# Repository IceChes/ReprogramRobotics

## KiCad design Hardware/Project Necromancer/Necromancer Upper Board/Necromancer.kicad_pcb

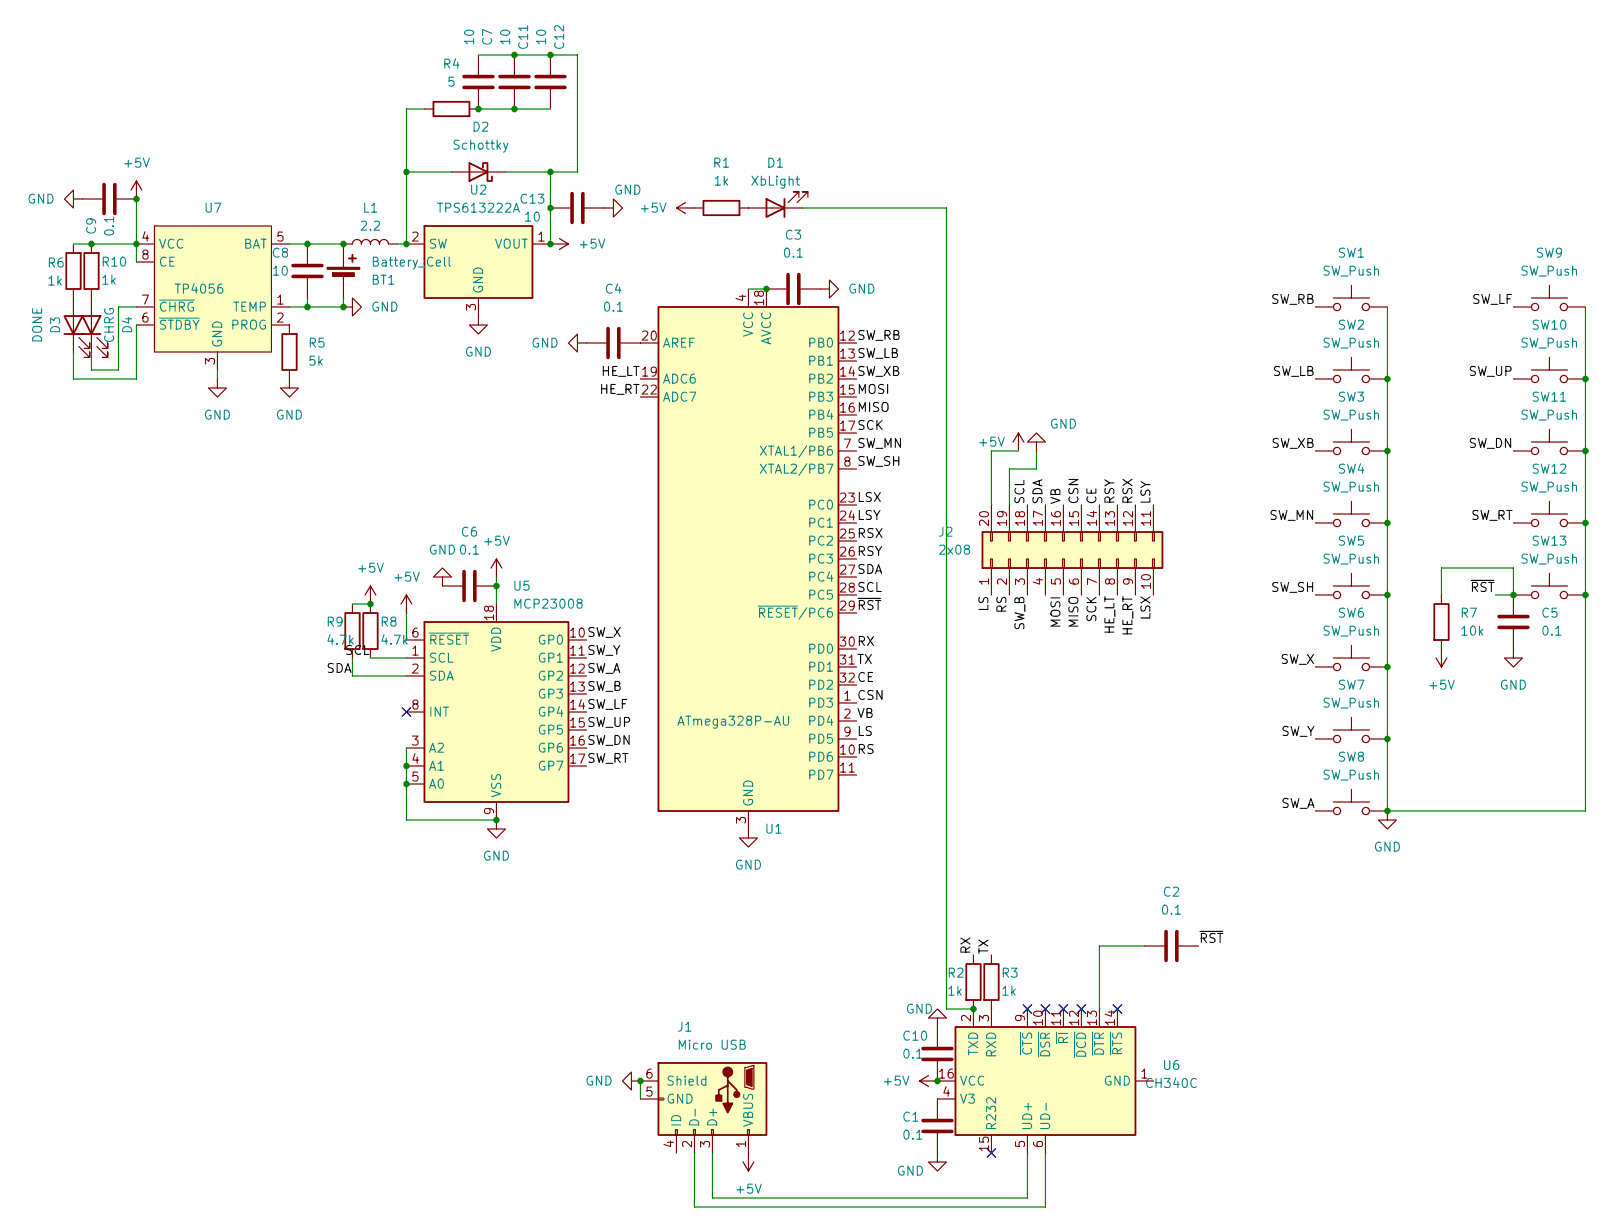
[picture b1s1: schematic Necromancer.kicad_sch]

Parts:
BT1: Battery_Cell; PinHeader_1x02_P2.54mm_Vertical
C1, C2, C3, C4, C5, C6, C9, C10: 0.1; C_0805_2012Metric
C7, C8, C11, C12, C13: 10; C_0805_2012Metric
D1: XbLight; LED_0805_2012Metric
D2: Schottky; D_SOD-323
D3: DONE; LED_0805_2012Metric
D4: CHRG; LED_0805_2012Metric
J1: Micro USB; USB_Micro-B_Amphenol_10118193-0001LF_Horizontal
J2: 2x08; PinHeader_2x10_P2.54mm_Vertical
L1: 2.2; L_2010_5025Metric
R1, R2, R3, R6, R10: 1k; R_0805_2012Metric
R4: 5; R_0805_2012Metric
R5: 5k; R_0805_2012Metric
R7: 10k; R_0805_2012Metric
R8, R9: 4.7k; R_0805_2012Metric
SW1, SW2: SW_Push; SW_Tactile_SPST_Angled_PTS645Vx31-2LFS
SW3: SW_Push; membraneSwitch_Large
SW4, SW5, SW6, SW7, SW8: SW_Push; membraneSwitch_Small
SW9, SW10, SW11, SW12: SW_Push; metaldome_7mm
SW13: SW_Push; SW_Push_1P1T_NO_Vertical_Wuerth_434133025816
U1: ATmega328P-AU; TQFP-32_7x7mm_P0.8mm
U2: TPS613222A; SOT-23
U5: MCP23008; SOIC-18W_7.5x11.6mm_P1.27mm
U6: CH340C; SOIC-16_3.9x9.9mm_P1.27mm
U7: TP4056; SOP-8_5.28x5.23mm_P1.27mm

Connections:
+5V: C6.2, C7.1, C9.1, C10.1, C11.1, C12.1, C13.1, D2.1 (K), J1.1 (VBUS), J2.20, R1.1, R6.2, R7.2, R8.1, R9.1, R10.2, U2.1 (VOUT), U5.6 (~RESET), U5.18 (VDD), U6.16 (VCC), U7.4 (VCC), U7.8 (CE)
/CE: J2.14, U1.32 (PD2)
/CSN: J2.15, U1.1 (PD3)
/HE_LT: J2.8, U1.19 (ADC6)
/HE_RT: J2.9, U1.22 (ADC7)
/LS: J2.1, U1.9 (PD5)
/LSX: J2.10, U1.23 (PC0)
/LSY: J2.11, U1.24 (PC1)
/MISO: J2.6, U1.16 (PB4)
/MOSI: J2.5, U1.15 (PB3)
/RS: J2.2, U1.10 (PD6)
/RSX: J2.12, U1.25 (PC2)
/RSY: J2.13, U1.26 (PC3)
/RX: R2.1, U1.30 (PD0)
/SCK: J2.7, U1.17 (PB5)
/SCL: J2.18, R8.2, U1.28 (PC5), U5.1 (SCL)
/SDA: J2.17, R9.2, U1.27 (PC4), U5.2 (SDA)
/SW_A: SW8.1, U5.12 (GP2)
/SW_B: J2.3, U5.13 (GP3)
/SW_DN: SW11.1, U5.16 (GP6)
/SW_LB: SW2.1, U1.13 (PB1)
/SW_LF: SW9.1, U5.14 (GP4)
/SW_MN: SW4.1, U1.7 (XTAL1/PB6)
/SW_RB: SW1.1, U1.12 (PB0)
/SW_RT: SW12.1, U5.17 (GP7)
/SW_SH: SW5.1, U1.8 (XTAL2/PB7)
/SW_UP: SW10.1, U5.15 (GP5)
/SW_X: SW6.1, U5.10 (GP0)
/SW_XB: SW3.1, U1.14 (PB2)
/SW_Y: SW7.1, U5.11 (GP1)
/TX: R3.1, U1.31 (PD1)
/VB: J2.16, U1.2 (PD4)
/~RST: C2.2, C5.1, R7.1, SW13.1, U1.29 (~RESET/PC6)
GND: BT1.2 (-), C1.1, C3.2, C4.1, C5.2, C6.1, C8.1, C9.2, C10.2, C13.2, J1.5 (GND), J1.6 (Shield), J2.19, R5.1, SW1.2, SW2.2, SW3.2, SW4.2, SW5.2, SW6.2, SW7.2, SW8.2, SW9.2, SW10.2, SW11.2, SW12.2, SW13.2, U1.3 (GND), U1.5 (GND), U1.21 (GND), U2.3 (GND), U5.3 (A2), U5.4 (A1), U5.5 (A0), U5.9 (VSS), U7.1 (TEMP), U7.3 (GND)
unnamed: BT1.1 (+), C8.2, L1.1, U7.5 (BAT)
unnamed: C7.2, C11.2, C12.2, R4.2
unnamed: D1.2 (A), R1.2
unnamed: D1.1 (K), R2.2, U6.2 (TXD)
unnamed: D2.2 (A), L1.2, R4.1, U2.2 (SW)
unnamed: D3.2 (A), R6.1
unnamed: D3.1 (K), U7.6 (~STDBY)
unnamed: D4.2 (A), R10.1
unnamed: D4.1 (K), U7.7 (~CHRG)
unnamed: J1.3 (D+), U6.5 (UD+)
unnamed: J1.2 (D-), U6.6 (UD-)
unnamed: C4.2, U1.20 (AREF)
unnamed: C3.1, U1.4 (VCC), U1.6 (VCC), U1.18 (AVCC)
unnamed: R3.2, U6.3 (RXD)
unnamed: C1.2, U6.4 (V3)
unnamed: C2.1, U6.13 (~DTR)
unnamed: R5.2, U7.2 (PROG)

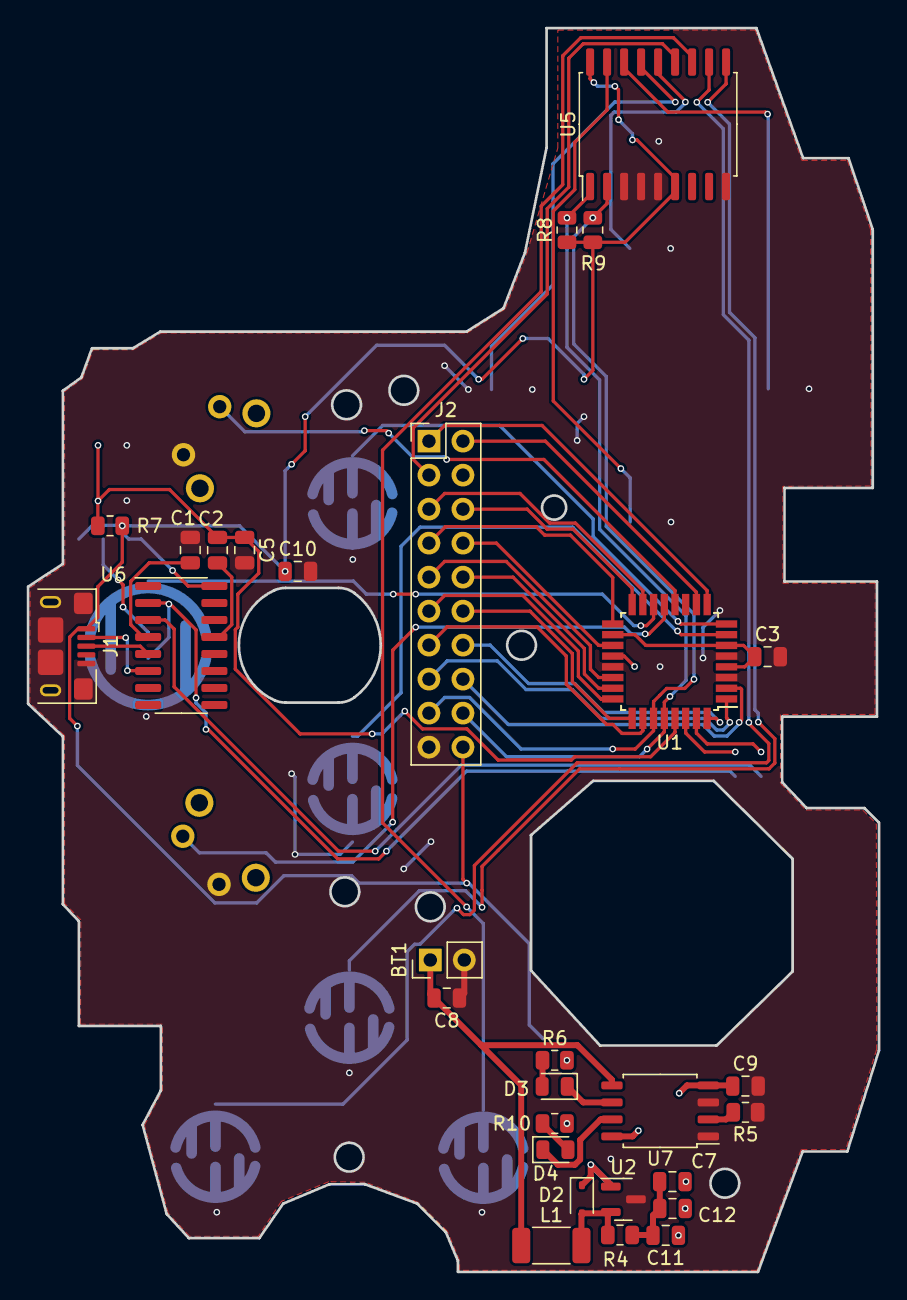
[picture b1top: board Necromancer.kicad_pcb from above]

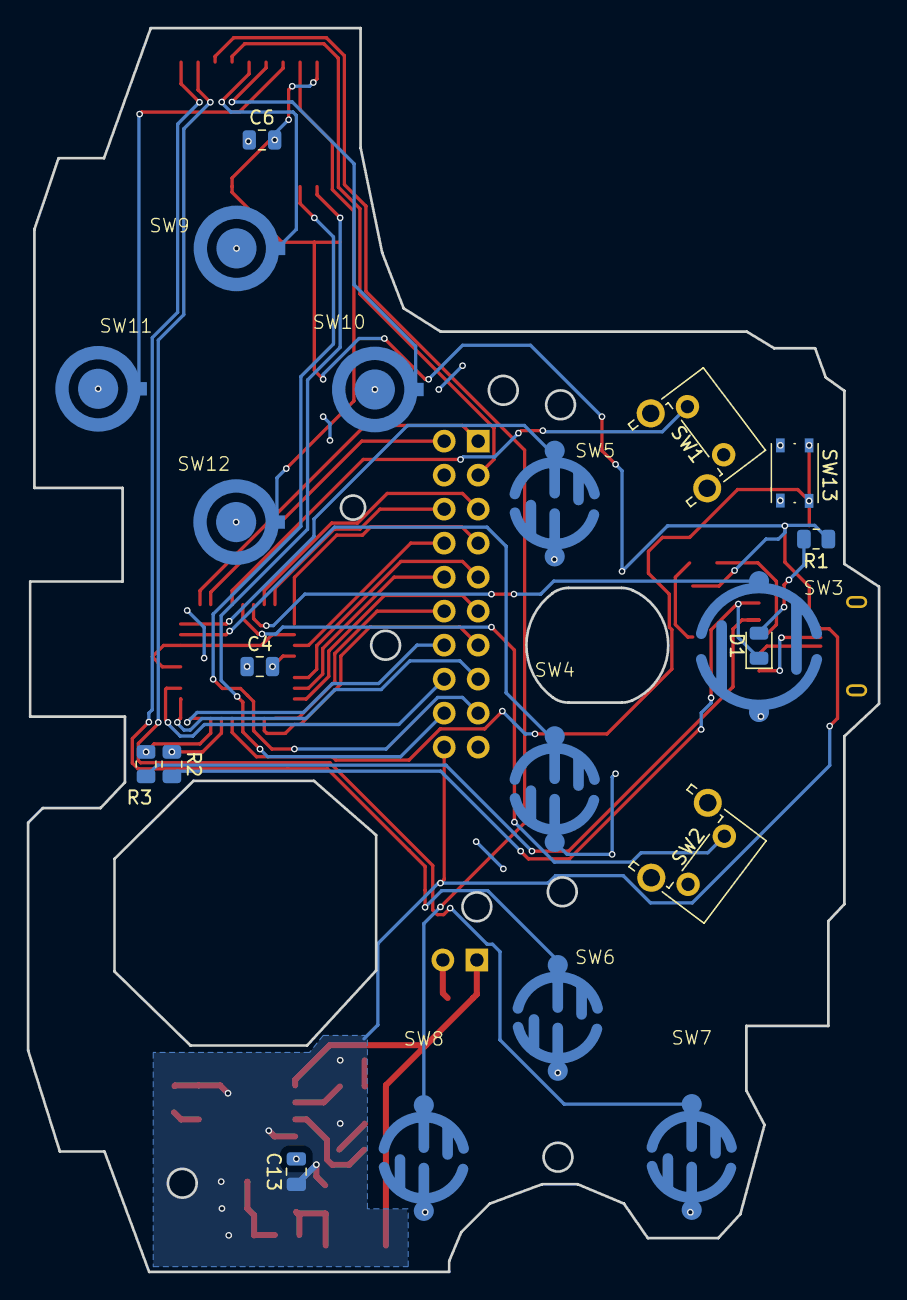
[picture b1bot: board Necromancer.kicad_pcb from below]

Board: 2 copper layers, 63.6 x 92.9 mm, 49 parts (20 on the bottom side), 51 nets.

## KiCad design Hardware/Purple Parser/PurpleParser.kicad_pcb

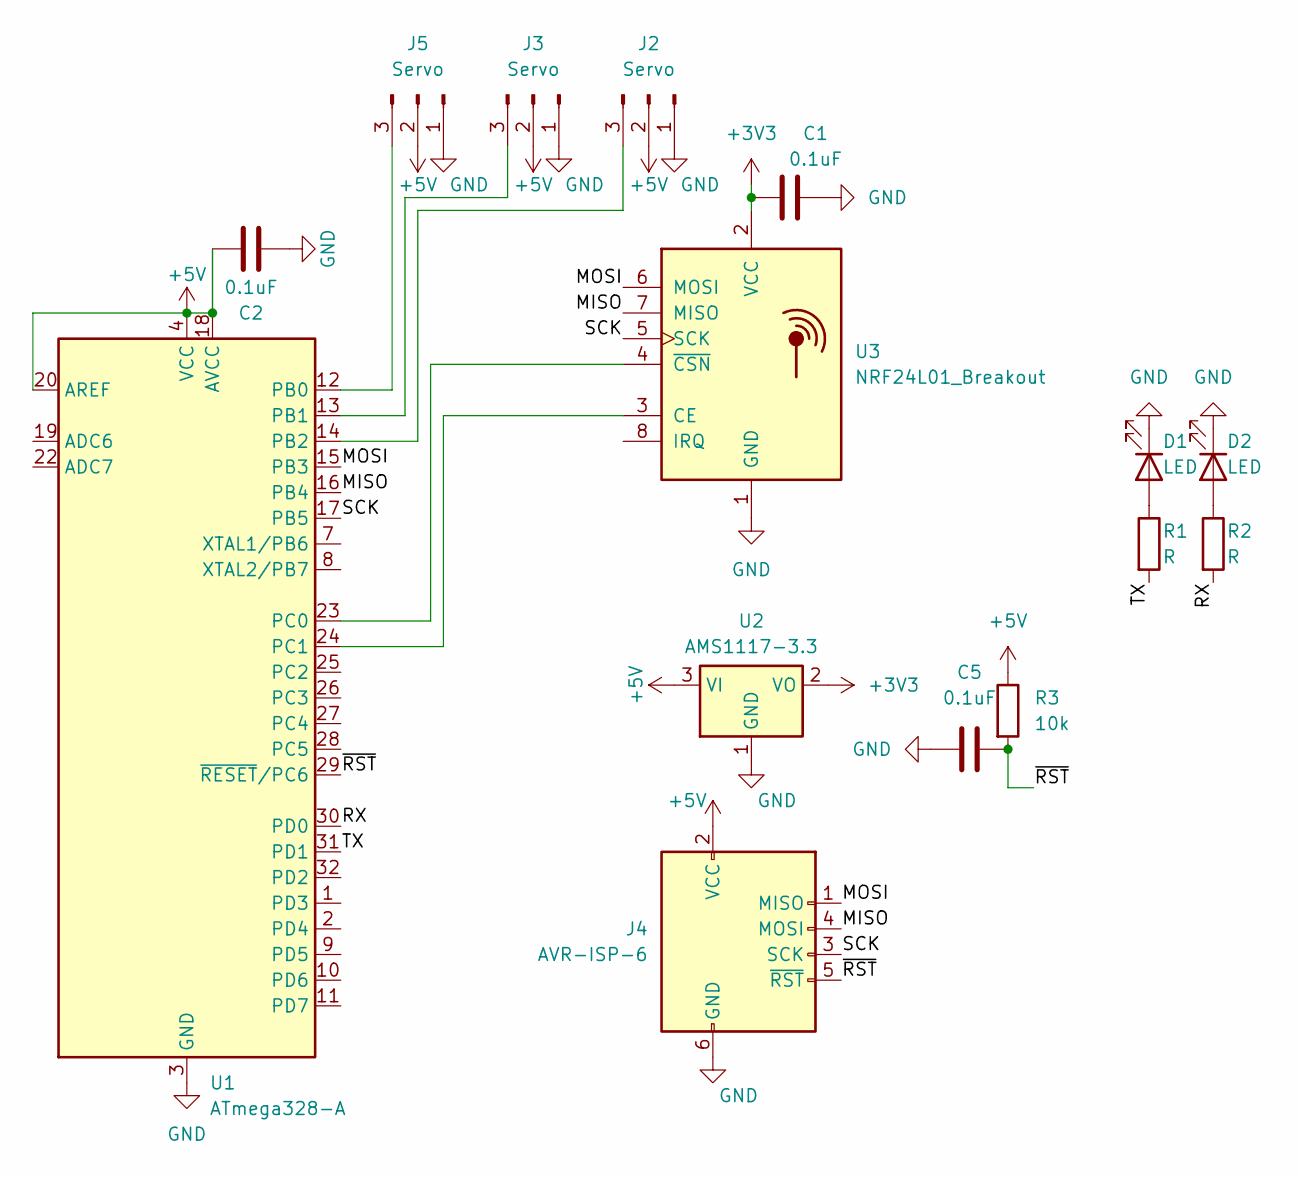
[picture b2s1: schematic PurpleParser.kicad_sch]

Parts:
C1, C2, C5: 0.1uF; C_0805_2012Metric
D1, D2: LED; LED_0805_2012Metric
J2, J3, J5: Servo; PinHeader_1x03_P2.54mm_Vertical
J4: AVR-ISP-6; PinHeader_2x03_P2.54mm_Vertical
R1, R2: R; R_0805_2012Metric
R3: 10k; R_0805_2012Metric
U1: ATmega328-A; VQFN-32-1EP_5x5mm_P0.5mm_EP3.5x3.5mm
U2: AMS1117-3.3; SOT-223-3_TabPin2
U3: NRF24L01_Breakout; PinSocket_2x04_P2.54mm_Vertical

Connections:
+3V3: C1.1, U2.2 (VO), U3.2 (VCC)
+5V: C2.2, J2.2, J3.2, J4.2 (VCC), J5.2, R3.1, U1.4 (VCC), U1.6 (VCC), U1.18 (AVCC), U1.20 (AREF), U2.3 (VI)
/MISO: J4.4 (MOSI), U1.16 (PB4), U3.7 (MISO)
/MOSI: J4.1 (MISO), U1.15 (PB3), U3.6 (MOSI)
/RX: R2.2, U1.30 (PD0)
/SCK: J4.3 (SCK), U1.17 (PB5), U3.5 (SCK)
/TX: R1.2, U1.31 (PD1)
/~RST: C5.2, J4.5 (~RST), R3.2, U1.29 (~RESET/PC6)
GND: C1.2, C2.1, C5.1, D1.1 (K), D2.1 (K), J2.1, J3.1, J4.6 (GND), J5.1, U1.3 (GND), U1.5 (GND), U1.21 (GND), U1.33, U2.1 (GND), U3.1 (GND)
unnamed: D1.2 (A), R1.1
unnamed: D2.2 (A), R2.1
unnamed: J2.3, U1.14 (PB2)
unnamed: J3.3, U1.13 (PB1)
unnamed: J5.3, U1.12 (PB0)
unnamed: U1.23 (PC0), U3.4 (~CSN)
unnamed: U1.24 (PC1), U3.3 (CE)

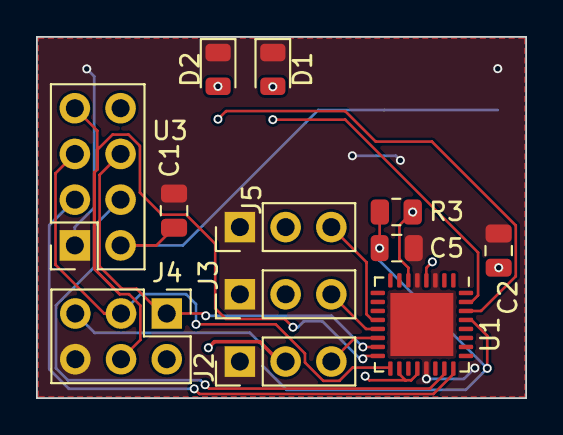
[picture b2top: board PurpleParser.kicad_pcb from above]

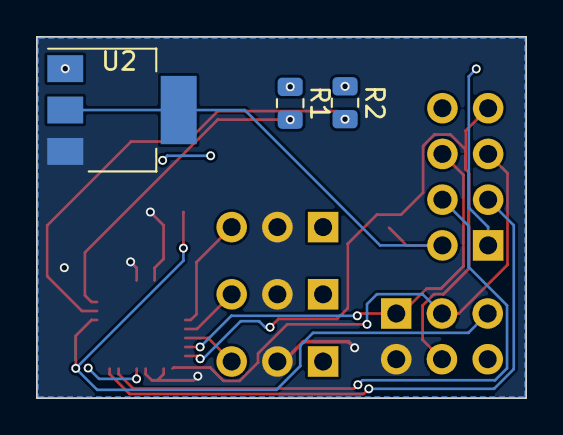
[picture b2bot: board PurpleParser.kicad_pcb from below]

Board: 2 copper layers, 27.2 x 20.1 mm, 15 parts (3 on the bottom side), 16 nets.

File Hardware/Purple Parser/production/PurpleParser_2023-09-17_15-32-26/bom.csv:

Designator,Footprint,Quantity,Value,LCSC Part #
"C1, C2, C5",0805,3,0.1uF,
"D1, D2",0805,2,LED,
"J2, J3, J5",PinHeader_1x03_P2.54mm_Vertical,3,Servo,
J4,PinHeader_2x03_P2.54mm_Vertical,1,AVR-ISP-6,
"R1, R2",0805,2,R,
R3,0805,1,10k,
U1,VQFN-32-1EP_5x5mm_P0.5mm_EP3.5x3.5mm,1,ATmega328-A,
U2,SOT-223-3_TabPin2,1,AMS1117-3.3,
U3,PinSocket_2x04_P2.54mm_Vertical,1,NRF24L01_Breakout,
